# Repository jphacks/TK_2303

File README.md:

# ホッとお風呂

## 製品概要
### 背景
少子高齢化の進行により来年には<strong>総人口の30％</strong>が高齢者(65歳以上)になることが見込まれています。それにより高齢者の一人暮らしや老老介護が社会問題となっています。

お風呂は非常に"不安"な場面の一つで、ヒートショックや溺死といった死亡リスクが高くなります。消費者庁の統計によると、お風呂場での年間の死亡者数は**19,000人**にも上ります。

そのようなお風呂という<strong>「危険な」</strong>場所を<strong>「ホッと一息できる」</strong>場所にしたいという思いでこのプロダクトを制作しました。

### 製品説明
このプロダクトは、ハードウェア、サーバー、モバイルアプリからなります。

ハードウェアはお風呂に取り付けることができ、気圧、温度、湿度、CO2、音圧センサが実装されています。それらのデータから、お風呂に入っているかどうかという状態を推定し、音圧から転倒などの危険を検知します。

長くお風呂に入っている時や大きな音が出た時は、サーバーを通してユーザーにそのことが通知されます。これにより事故を未然に防いだり、万が一事故が発生したとしてもいち早く察知することができます。

### 特長
#### 1. プライバシー保護
お風呂はプライバシーが尊重される場所なので、カメラやミリ波レーダセンサ、マイクなどを設置することに抵抗を感じる方も多いでしょう。そこで音圧や気圧、湿度の情報から入浴中かどうかのステータスを検知し、必要最低限の情報をサーバーに送っています。

#### 2. モバイルアプリでのリアルタイムな危険検知
お風呂で異常が検知された場合、即座にスマートフォンにPush通知が送られ、異常に気づくことができます。そして、予め登録した緊急連絡先に電話をすることが可能になっています。

アプリを使い慣れないユーザーにとっても使いやすく、音と振動、アニメーションを有効に使いインタラクティブなUI/UXを実現しています。

#### 3. 高精度な入浴、異常検知
入浴や異常を高精度に検知し、サーバーにデータを送っています。

### 解決出来ること
このプロダクトによってお風呂場における高齢者の事故を早期に検知することができ、死亡リスクを激減させられると考えています。

### 今後の展望
このプロダクトを発展させて、家全体で転倒等による事故を検出できるようにし「高齢者の方のためのスマートホーム」を実現したいと考えています。

### 注力したこと
* ハッカソンの期間内に、ユーザーがどんな課題を持っていて、どのようにアプローチするといいか検討を入念に行なったこと
* 開発メンバー3人でアプリ、サーバ、ハードウェアを分担し、それぞれのインターフェースについての情報を共有することで効率良く開発を進めたこと

## 開発技術
### 活用した技術

#### アプリ
* Swift
* Apple Push Notification Server

#### サーバ
* Cloudflare Workers
* Workers KV
* Firebase Cloud Messaging
* GitHub ActionsでAPIドキュメントをビルドし、[GitHub Pagesで公開](https://jphacks.github.io/TK_2303/api-document.html)

#### デバイス
* ESP32
* 温度、気圧、湿度、CO2センサ(BME280)
* PDMマイク(SPH0641LU4H)
* FreeRTOS

### 独自技術
#### ハッカソンで開発した独自機能・技術
* 独自で開発したものの内容をこちらに記載してください
* [ESP32でPDMマイクを直接読み取るコード](https://github.com/jphacks/TK_2303/blob/master/hardware/device/Mic.h)
  * ESP32のライブラリの仕様が変わった影響でネット上の情報が当てにならず苦労した
* [Cloudflare Workers上でのFirebaseの利用](https://github.com/jphacks/TK_2303/blob/d92fb7b4c212a5a55339ab0f3a365487967f2cfd/backend/src/model.ts#L114)
  * Firebaseの公式ライブラリはNode.jsのAPIに依存しておりCloudflare Workersからは利用できない。そこでOAuth2の認証から自前で実装し、Firebaseの通知APIを利用できるようにした。

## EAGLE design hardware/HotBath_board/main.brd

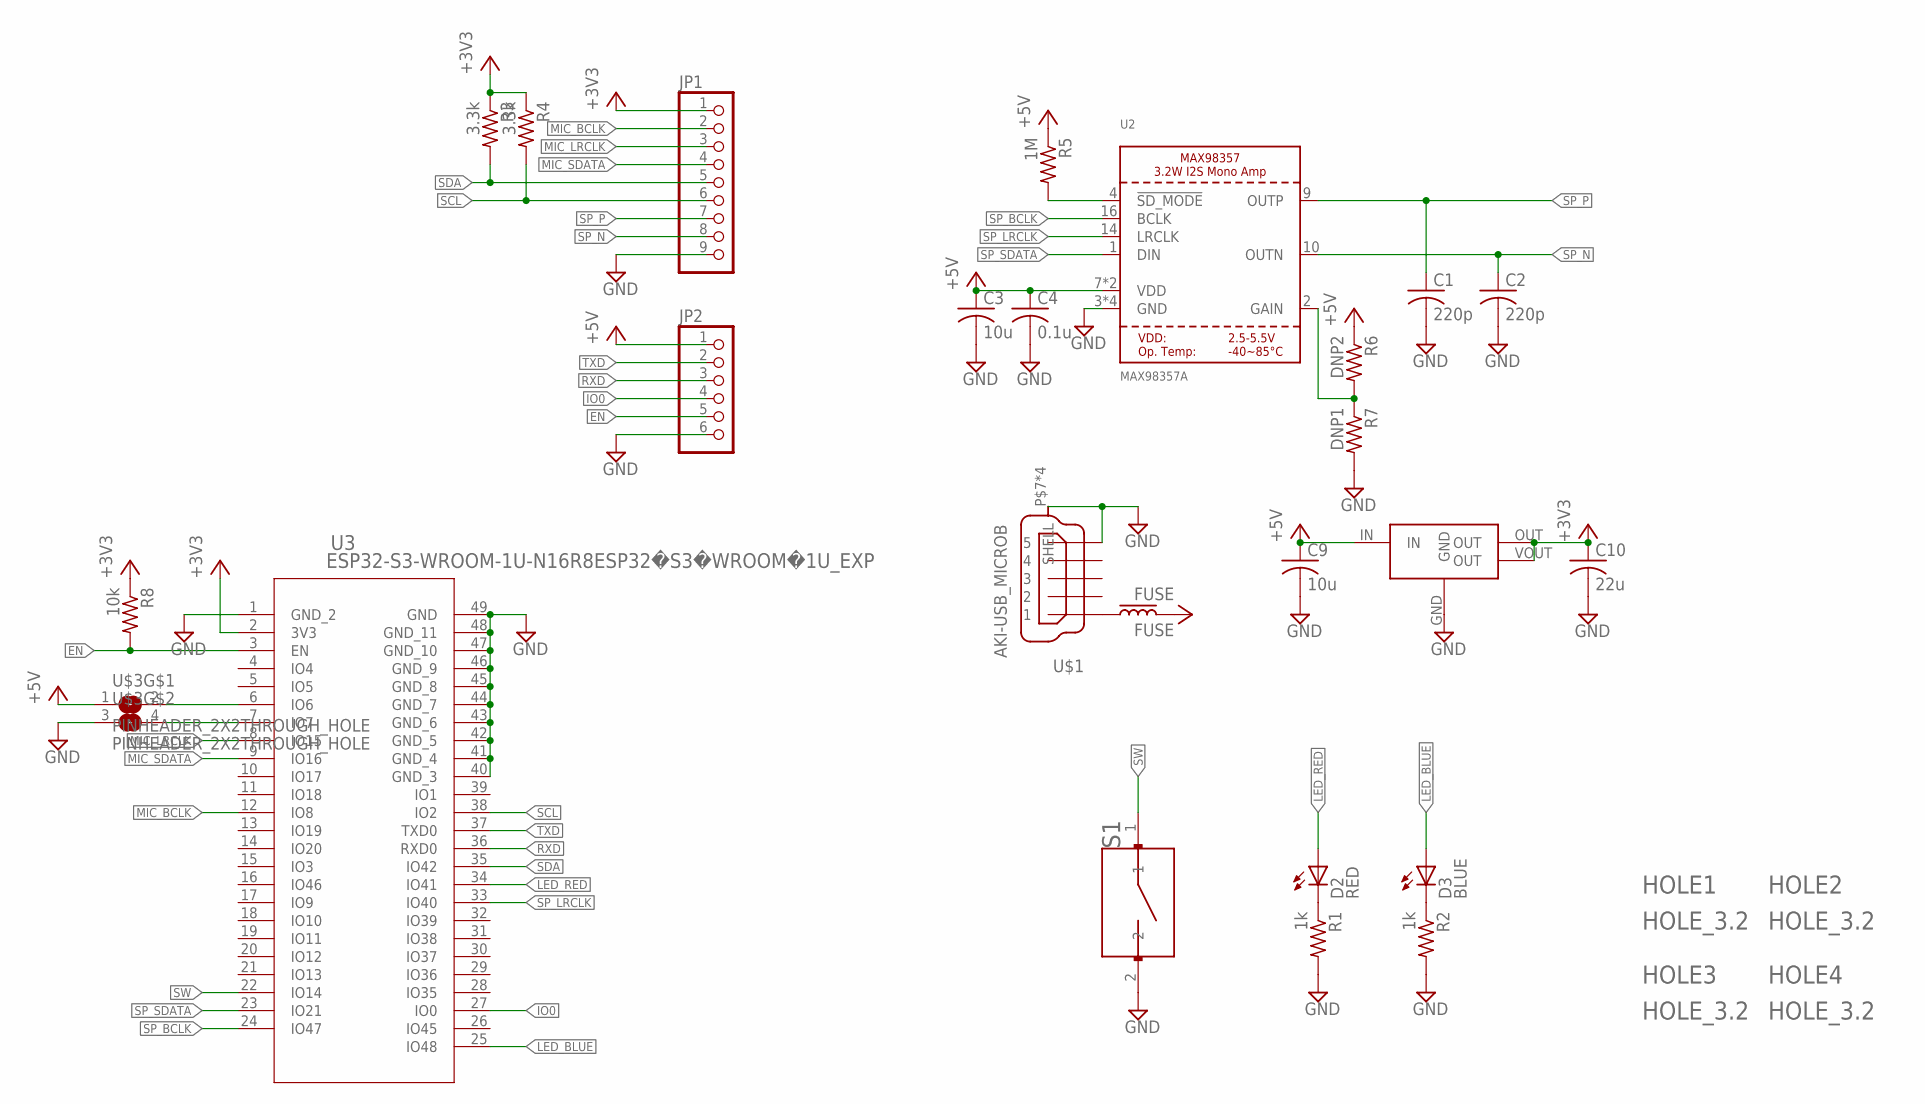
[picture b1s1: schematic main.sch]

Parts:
C1, C2: 220p; 2012-C
C3, C9: 10u; 2012-C
C4: 0.1u; 2012-C
C10: 22u; 2012-C
D2: RED; D2012
D3: BLUE; D2012
FUSE: FUSE; 2012-C
HOLE1, HOLE2, HOLE3, HOLE4: HOLE_3.2
IC2: AZ1117H-ADJ; SOT223
JP1: PINHD-1X9; 1X09
JP2: PINHD-1X6; 1X06
R1, R2: 1k; 2012-R
R3, R4: 3.3k; 2012-R
R5: 1M; 2012-R
R6: DNP2; 2012-R
R7: DNP1; 2012-R
R8: 10k; 2012-R
S1: TACTSW_SMD; SW_B3U-1000P
U2: MAX98357A; QFN16_3MM
U3: ESP32-S3-WROOM-1U-N16R8ESP32�S3�WROOM�1U_EXP; ESP32�S3�WROOM�1U_EXP
U$1: AKI-USB_MICROB; ZX62R_B
U$3: PINHEADER_2X2THROUGH_HOLE; 2X02

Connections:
+3V3: C10.1, IC2.OUT, IC2.VOUT (OUT), JP1.1, R3.1, R4.1, R8.1, U3.2 (3V3)
+5V: C3.1, C4.1, C9.1, FUSE.2, IC2.IN, JP2.1, R5.1, R6.1, U2.7 (VDD), U2.8 (VDD), U$3.1
EN: JP2.5, R8.2, U3.3 (EN)
GND: C1.2, C2.2, C3.2, C4.2, C9.2, C10.2, IC2.GND, JP1.9, JP2.6, R1.2, R2.2, R7.2, S1.2, U2.3 (GND), U2.11 (GND), U2.15 (GND), U2.THERMAL (GND), U3.1 (GND_2), U3.40 (GND_3), U3.41 (GND_4), U3.42 (GND_5), U3.43 (GND_6), U3.44 (GND_7), U3.45 (GND_8), U3.46 (GND_9), U3.47 (GND_10), U3.48 (GND_11), U3.49 (GND), U$1.5, U$1.P$7 (SHELL), U$1.P$8 (SHELL), U$1.P$9 (SHELL), U$1.SH (SHELL), U$3.3 (1)
IO0: JP2.4, U3.27 (IO0)
LED_BLUE: D3.A, U3.25 (IO48)
LED_RED: D2.A, U3.34 (IO41)
MIC_BCLK: JP1.2, U3.12 (IO8)
MIC_LRCLK: JP1.3, U3.8 (IO15)
MIC_SDATA: JP1.4, U3.9 (IO16)
unnamed: D3.K, R2.1
unnamed: FUSE.1, U$1.1
unnamed: D2.K, R1.1
unnamed: R6.2, R7.1, U2.2 (GAIN)
unnamed: U3.6 (IO6), U$3.2
unnamed: R5.2, U2.4 (!SD_MODE)
unnamed: U3.7 (IO7), U$3.4 (2)
RXD: JP2.3, U3.36 (RXD0)
SCL: JP1.6, R4.2, U3.38 (IO2)
SDA: JP1.5, R3.2, U3.35 (IO42)
SP_BCLK: U2.16 (BCLK), U3.24 (IO47)
SP_LRCLK: U2.14 (LRCLK), U3.33 (IO40)
SP_N: C2.1, JP1.8, U2.10 (OUTN)
SP_P: C1.1, JP1.7, U2.9 (OUTP)
SP_SDATA: U2.1 (DIN), U3.23 (IO21)
SW: S1.1, U3.22 (IO14)
TXD: JP2.2, U3.37 (TXD0)

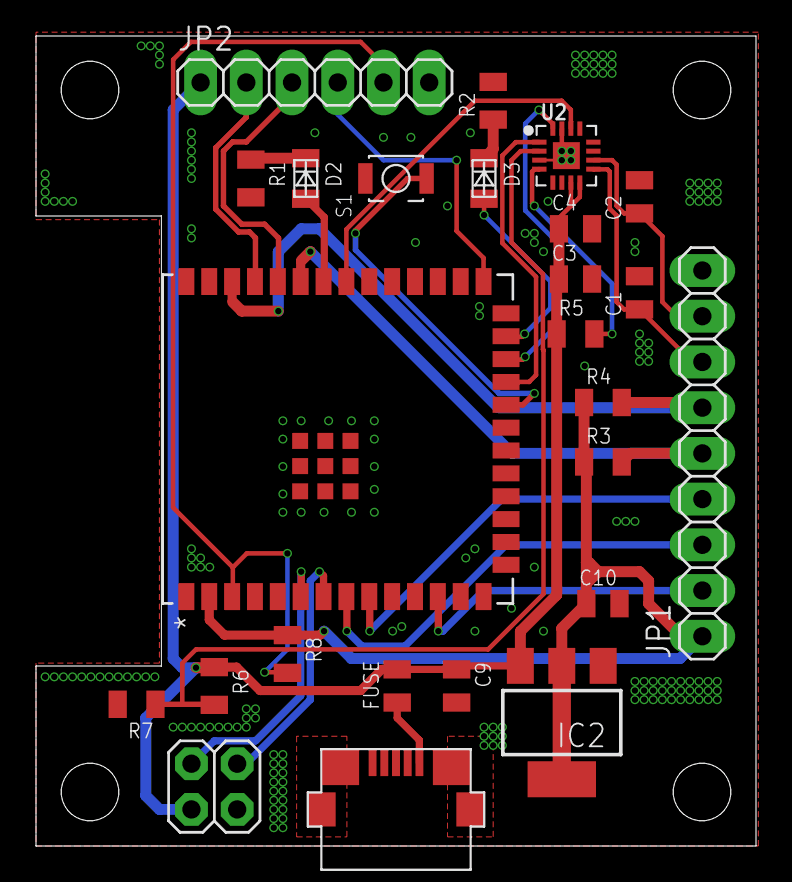
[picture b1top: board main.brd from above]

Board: 2 copper layers, 40.0 x 45.0 mm, 29 parts (0 on the bottom side), 27 nets.

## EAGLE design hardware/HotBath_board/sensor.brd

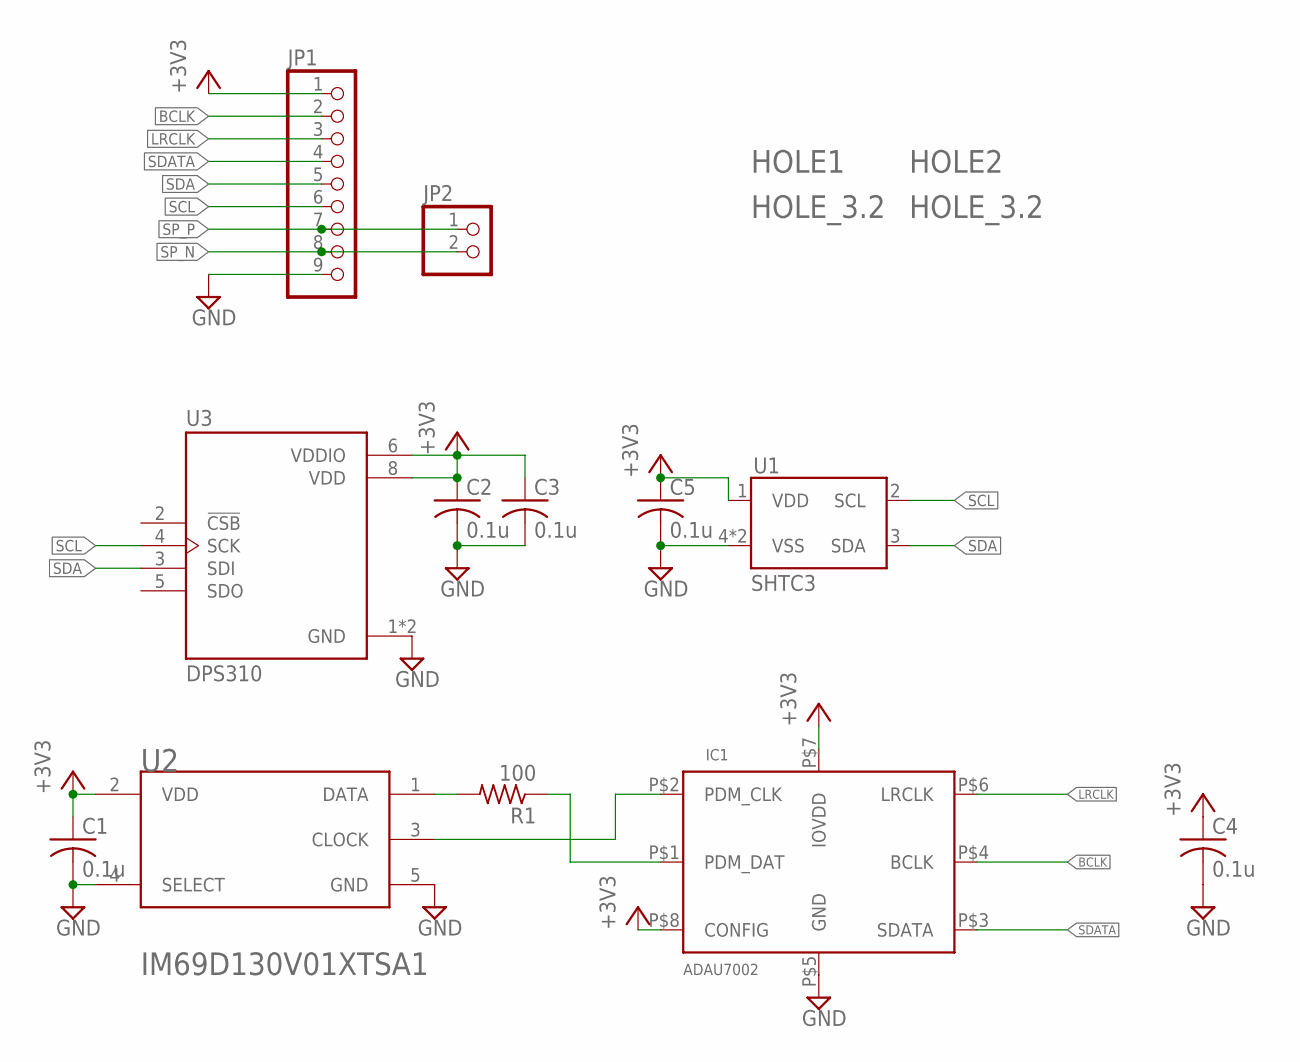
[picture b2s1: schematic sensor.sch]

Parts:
C1, C2, C3, C4, C5: 0.1u; 2012-C
HOLE1, HOLE2: HOLE_3.2
IC1: ADAU7002; WLCSP2X4
JP1: PINHD-1X9; 1X09
JP2: PINHD-1X2; 1X02
R1: 100; 2012-R
U1: SHTC3
U2: IM69D130
U3: DPS310; XDCR_DPS310

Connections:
+3V3: C1.1, C2.1, C3.1, C4.1, C5.1, IC1.P$7 (IOVDD), IC1.P$8 (CONFIG), JP1.1, U1.1 (VDD), U2.2 (VDD), U3.6 (VDDIO), U3.8 (VDD)
BCLK: IC1.P$4 (BCLK), JP1.2
GND: C1.2, C2.2, C3.2, C4.2, C5.2, IC1.P$5 (GND), JP1.9, U1.4 (VSS), U1.5 (VSS), U2.4 (SELECT), U2.5 (GND), U3.1 (GND), U3.7 (GND)
LRCLK: IC1.P$6 (LRCLK), JP1.3
unnamed: R1.2, U2.1 (DATA)
unnamed: IC1.P$1 (PDM_DAT), R1.1
unnamed: IC1.P$2 (PDM_CLK), U2.3 (CLOCK)
SCL: JP1.6, U1.2 (SCL), U3.4 (SCK)
SDA: JP1.5, U1.3 (SDA), U3.3 (SDI)
SDATA: IC1.P$3 (SDATA), JP1.4
SP_N: JP1.8, JP2.2
SP_P: JP1.7, JP2.1

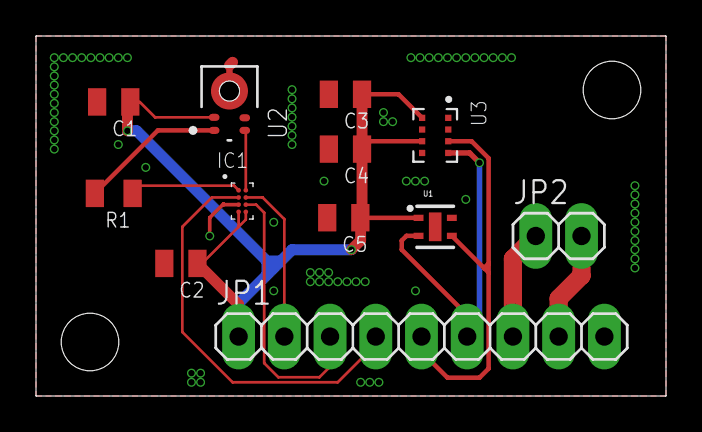
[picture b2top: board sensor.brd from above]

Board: 2 copper layers, 35.0 x 20.0 mm, 14 parts (0 on the bottom side), 12 nets.

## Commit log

2023-10-28 add Swift to gitignore
2023-10-28 initial commit for iOS
2023-10-28 make main page ui
2023-10-28 make viewModel
2023-10-28 fix network
2023-10-28 make alertView
2023-10-28 Add backend
2023-10-28 add calling feature
2023-10-28 setup notification
2023-10-28 make alert
2023-10-28 add NotificationListView
2023-10-28 Update backend
2023-10-28 make README
2023-10-29 Add upload API document action
2023-10-29 Update apischema
2023-10-29 Fix workflow
2023-10-29 Setup actions (#3)
    * Add upload API document action
    * Update openapi.yml
    * Update apischema
    * Update apischema
    * Fix workflow
    * Fix workflow
2023-10-29 README.md を更新
2023-10-29 make history
2023-10-29 FW一旦完成
2023-10-29 fix detail
2023-10-29 refactor model classes
2023-10-29 refactor views
2023-10-29 refactor viewModel
2023-10-29 add pdf
2023-11-03 make onboardingView frame
2023-11-04 onboarding Views main wireframe
2023-11-04 Migration to platformio
2023-11-04 freertos化
2023-11-04 increase stack size
2023-11-04 implement config
2023-11-04 add recursive mutex
2023-11-04 make bluetooth onboarding
2023-11-04 implement ble
2023-11-04 make fifthView
2023-11-07 add binary
2023-11-07 online update
2023-11-08 fix Bluetooth
2023-11-11 Sensor operation check completed
2023-11-12 implement led indicator
2023-11-12 fix conflict
2023-11-12 fix onboarding
2023-11-12 add token
2023-11-12 fix request
2023-11-12 add settingView
2023-11-12 implement onbording procedure
2023-11-12 libpeer
2023-11-13 esp-idf
2023-11-15 implement bathing judge
2023-11-16 implement wav & mic
2023-11-16 update version
2023-11-16 fix for preview
2023-11-16 background notification management
2023-11-16 add preview datas
2023-11-16 fix background
2023-11-17 get latest firmware
2023-11-17 fix eeprom bug
2023-11-17 add send fcm token
2023-11-17 add board
2023-11-18 speaker
2023-11-18 Add lambda function
2023-11-18 Edit makefile
2023-11-18 reset after speaker
2023-11-18 Add Dockerfile
2023-11-18 add onboarding picture
2023-11-18 add #if DEBUG
2023-11-18 send alert
2023-11-18 fix bug
2023-11-18 long push
2023-11-18 add Setting page
2023-11-18 Update lambda function
2023-11-18 change sound data
2023-11-18 Use dockerfile to build lambda func
2023-11-18 for demo
2023-11-18 demo macro
2023-11-26 fix gitignore

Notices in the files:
parts and their libraries:
microbuilder: This work is placed in the public domain, and may be freely used for commercial and non-commercial work with the following conditions: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
COPYRIGHT: Copyright (C) 2023 Ultra Librarian. All rights reserved.
